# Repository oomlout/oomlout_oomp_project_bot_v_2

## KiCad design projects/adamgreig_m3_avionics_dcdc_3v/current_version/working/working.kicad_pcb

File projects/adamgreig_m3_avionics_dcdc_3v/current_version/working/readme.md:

# m3_avionics
 
## summary 
* id: adamgreig_m3_avionics_dcdc_3v
* user: adamgreig
* name: m3_avionics
* board: dcdc_3v
* repo: https://github.com/adamgreig/m3-avionics
* src_file_repo_kicad_pcb: m3psu/pcb/DCDC-3V/DCDC-3V.kicad_pcb
* src_file_repo_kicad_pcb_link: https://github.com/adamgreig/m3-avionics/tree/master/m3psu/pcb/DCDC-3V/DCDC-3V.kicad_pcb

* src_file_repo_sch: m3psu/pcb/DCDC-3V/DCDC-3V.sch
* src_file_repo_sch_link: https://github.com/adamgreig/m3-avionics/tree/master/m3psu/pcb/DCDC-3V/DCDC-3V.sch
* full details link: https://github.com/oomlout/oomlout_oomp_project_bot_v_2/tree/main/projects/adamgreig_m3_avionics_dcdc_3v/current_version/working  

## schematic  
  
[schematic (pdf)](working_schematic.pdf) 

## pcb  

[board (pdf)](working.pdf)  

## working_bom
| Id | Designator | Footprint | Quantity | Designation | Supplier and ref |  | None | 
| --- | --- | --- | --- | --- | --- | --- | --- | 
| 1 | J1 | TFML-110-02-L-D | 1 | WEST TOP |  |  | [''] | 
| 2 | J4 | TFML-110-02-L-D | 1 | EAST TOP |  |  | [''] | 
| 3 | J3 | TFML-105-02-L-D | 1 | NORTH TOP |  |  | [''] | 
| 4 | C5 | 0805 | 1 | 10u |  |  | [''] | 
| 5 | C6,C11,C1,C3,C4,C9,C12 | 0402 | 7 | 100n |  |  | [''] | 
| 6 | C7 | 0402 | 1 | 3n3 |  |  | [''] | 
| 7 | C8,C13 | 0805 | 2 | 22u |  |  | [''] | 
| 8 | C10,C2 | 0402 | 2 | 10n |  |  | [''] | 
| 9 | IC2 | QFN-16-EP-TI | 1 | TPS62132 |  |  | [''] | 
| 10 | IC1,IC3 | QFN-64-EP-LTC-UP | 2 | LTC2975 |  |  | [''] | 
| 11 | R2,R3,R4,R5,R6,R7,R8,R21,R22,R23,R24,R25,R27,R28 | 0402 | 14 | 10k |  |  | [''] | 
| 12 | R9,R10,R11,R12,R13,R14,R15,R16,R29,R30,R32,R33 | 0402 | 12 | 33k |  |  | [''] | 
| 13 | Q5,Q6,Q7,Q8,Q10,Q12 | SON2x2 | 6 | PFET_GDS |  |  | [''] | 
| 14 | R17,R18,R19,R20,R31,R34 | 0603 | 6 | 10m |  |  | [''] | 
| 15 | R1,R26 | 0402 | 2 | 5k49 |  |  | [''] | 
| 16 | Q1,Q2,Q3,Q4,Q9,Q11 | PowerPAK-SC-75-6L-Single | 6 | NFET_GDS |  |  | [''] | 
| 17 | L1 | XFL4020 | 1 | 2u2 |  |  | [''] | 
| 18 | R35,R36,R37,R38,R39,R40 | 0402 | 6 | 1M |  |  | [''] | 
| 19 | TP1,TP2,TP3,TP4 | TESTPAD | 4 | TESTPAD |  |  | [''] | 
| 20 | J2 | SFML-110-02-L-D-LC | 1 | WEST BOT |  |  | [''] | 
| 21 | J5 | SFML-110-02-L-D-LC | 1 | EAST BOT |  |  | [''] | 
| 22 | J6 | SFML-105-02-L-D-LC | 1 | NORTH BOT |  |  | [''] | 
| 23 | G*** | cusf_logo_full | 1 | LOGO |  |  | [''] | 

## bom_schematic
| Ref | Qnty | Value | Cmp name | Footprint | Description | Vendor | DNP | 
| --- | --- | --- | --- | --- | --- | --- | --- | 
| C1, C3, C4, C6, C9, C11, C12 | 7 | 100n | C | agg:0402 |  |  |  | 
| C2, C10 | 2 | 10n | C | agg:0402 |  |  |  | 
| C5 | 1 | 10u | C | agg:0805 |  |  |  | 
| C7 | 1 | 3n3 | C | agg:0402 |  |  |  | 
| C8, C13 | 2 | 22u | C | agg:0805 |  |  |  | 
| IC1, IC3 | 2 | LTC2975 | LTC2975 | agg:QFN-64-EP-LTC-UP |  |  |  | 
| IC2 | 1 | TPS62132 | TPS62132 | agg:QFN-16-EP-TI |  |  |  | 
| J1 | 1 | WEST TOP | CONN_02x10 | agg:TFML-110-02-L-D |  |  |  | 
| J2 | 1 | WEST BOT | CONN_02x10 | agg:SFML-110-02-L-D-LC |  |  |  | 
| J3 | 1 | NORTH TOP | CONN_02x05 | agg:TFML-105-02-L-D |  |  |  | 
| J4 | 1 | EAST TOP | CONN_02x10 | agg:TFML-110-02-L-D |  |  |  | 
| J5 | 1 | EAST BOT | CONN_02x10 | agg:SFML-110-02-L-D-LC |  |  |  | 
| J6 | 1 | NORTH BOT | CONN_02x05 | agg:SFML-105-02-L-D-LC |  |  |  | 
| L1 | 1 | 2u2 | L | agg:XFL4020 |  |  |  | 
| Q1, Q2, Q3, Q4, Q9, Q11 | 6 | NFET_GDS | NFET_GDS | agg:PowerPAK-SC-75-6L-Single |  |  |  | 
| Q5, Q6, Q7, Q8, Q10, Q12 | 6 | PFET_GDS | PFET_GDS | agg:SON2x2 |  |  |  | 
| R1, R26 | 2 | 5k49 | R | agg:0402 |  |  |  | 
| R2, R3, R4, R5, R6, R7, R8, R21, R22, R23, R24, R25, R27, R28 | 14 | 10k | R | agg:0402 |  |  |  | 
| R9, R10, R11, R12, R13, R14, R15, R16, R29, R30, R32, R33 | 12 | 33k | R | agg:0402 |  |  |  | 
| R17, R18, R19, R20, R31, R34 | 6 | 10m | R | agg:0603 |  |  |  | 
| R35, R36, R37, R38, R39, R40 | 6 | 1M | R | agg:0402 |  |  |  | 
| TP1, TP2, TP3, TP4 | 4 | TESTPAD | TESTPAD | agg:TESTPAD |  |  |  |

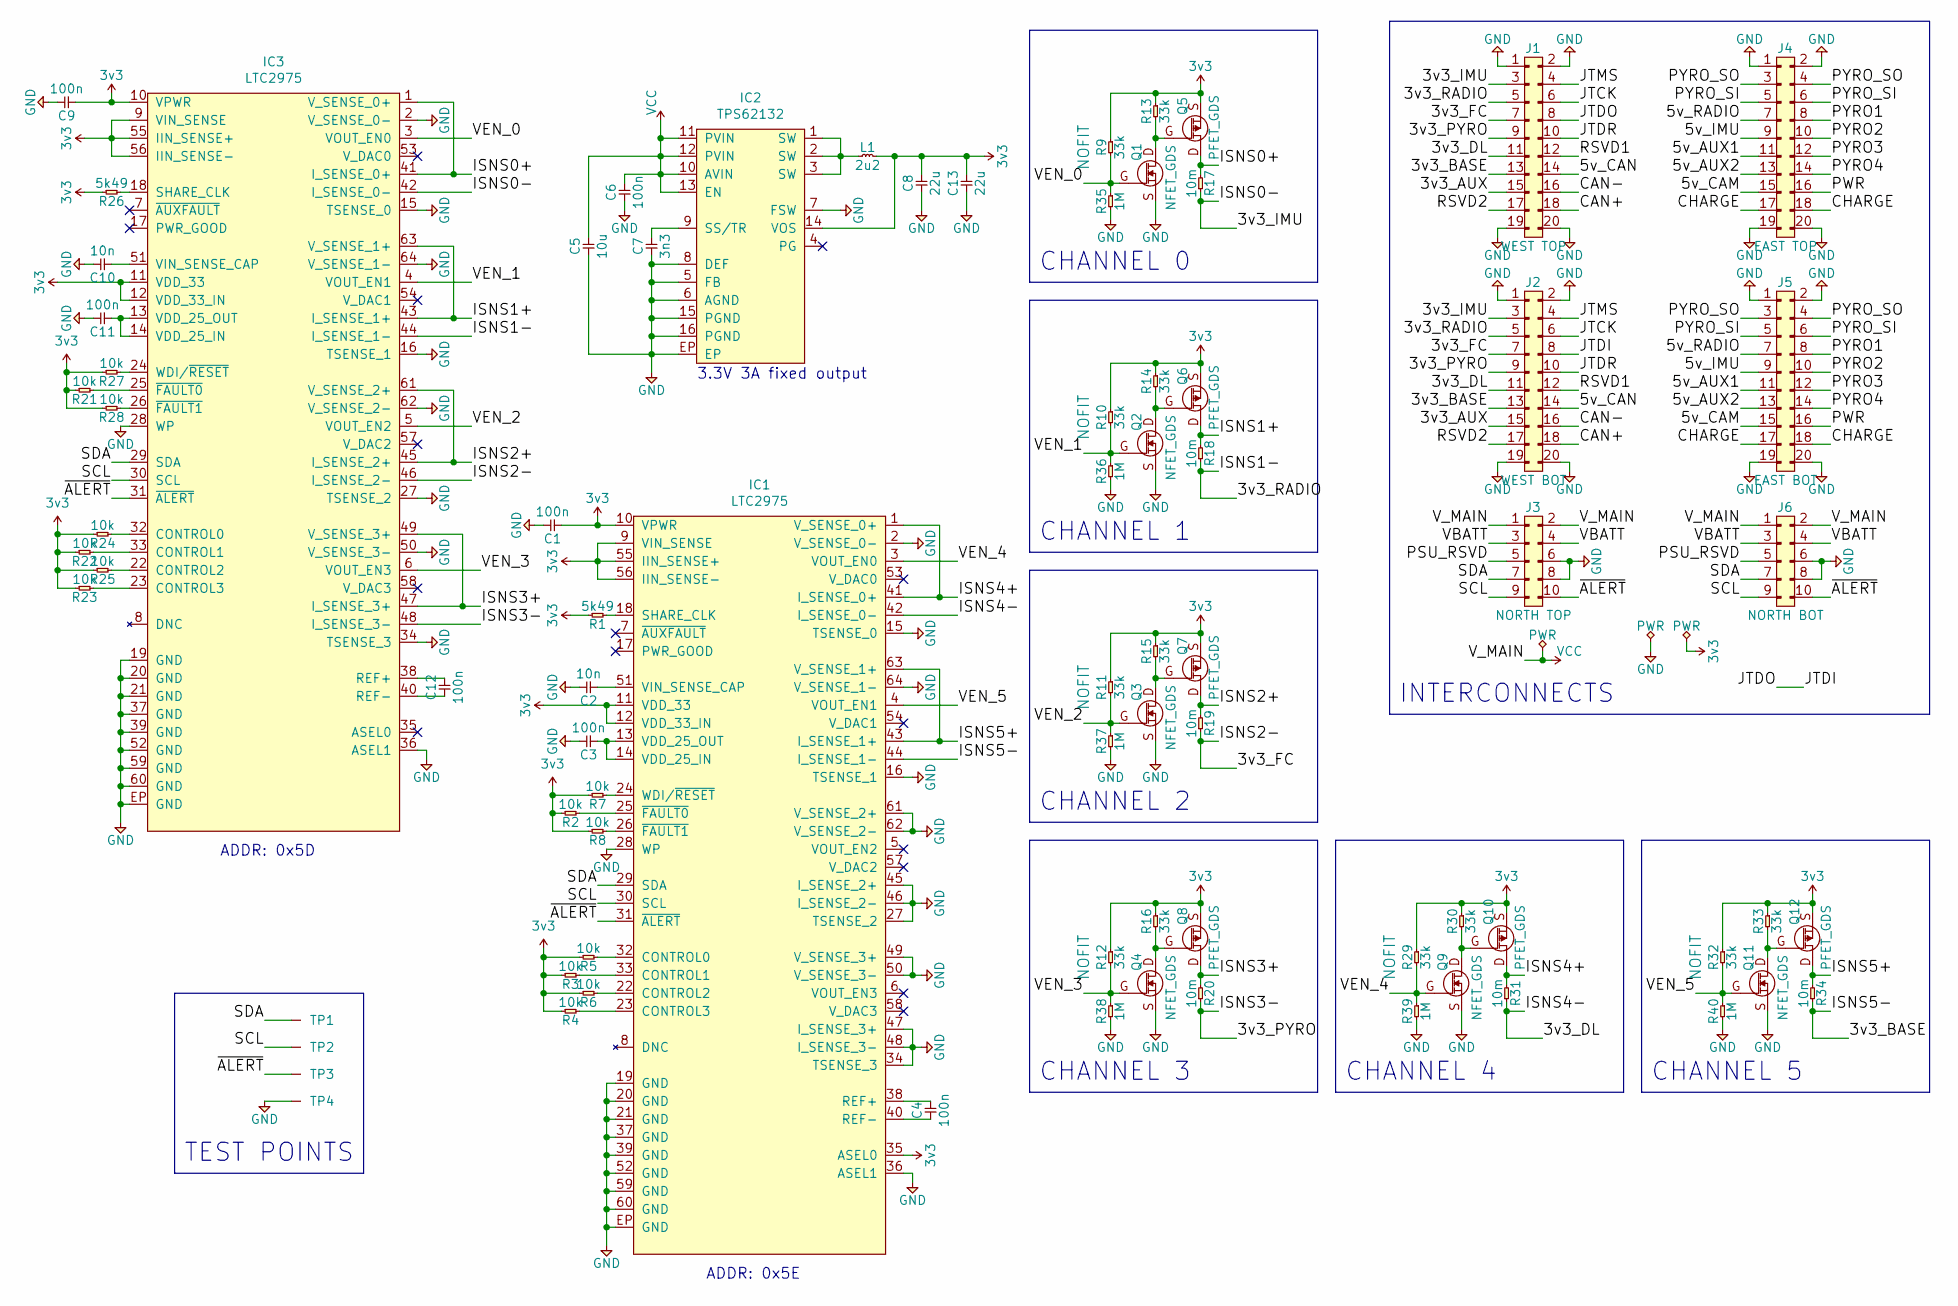
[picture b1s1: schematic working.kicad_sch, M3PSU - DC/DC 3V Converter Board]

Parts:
C1, C3, C4, C6, C9, C11, C12: 100n; 0402; Farnell 2496771
C2, C10: 10n; 0402; Farnell 1758924
C5: 10u; 0805; Farnell 2320856
C7: 3n3; 0402; Farnell 1758918
C8, C13: 22u; 0805; Farnell 1907510
IC1, IC3: LTC2975; QFN-64-EP-LTC-UP; Farnell 2461150
IC2: TPS62132; QFN-16-EP-TI; Farnell 2492468
J1: WEST TOP; TFML-110-02-L-D
J2: WEST BOT; SFML-110-02-L-D-LC
J3: NORTH TOP; TFML-105-02-L-D
J4: EAST TOP; TFML-110-02-L-D
J5: EAST BOT; SFML-110-02-L-D-LC
J6: NORTH BOT; SFML-105-02-L-D-LC
L1: 2u2; XFL4020; Farnell 2289216
Q1, Q2, Q3, Q4, Q9, Q11: NFET_GDS; PowerPAK-SC-75-6L-Single; Farnell 2364070
Q5, Q6, Q7, Q8, Q10, Q12: PFET_GDS; SON2x2; Farnell 2501102
R1, R26: 5k49; 0402; Farnell 2670533
R2, R3, R4, R5, R6, R7, R8, R21, R22, R23, R24, R25, R27, R28: 10k; 0402; Farnell 2447096
R9, R10, R11, R12, R29, R32: 33k; 0402
R13, R14, R15, R16, R30, R33: 33k; 0402; Farnell 2447160
R17, R18, R19, R20, R31, R34: 10m; 0603; Farnell RE05965
R35, R36, R37, R38, R39, R40: 1M; 0402; Farnell 2447127
TP1, TP2, TP3, TP4: TESTPAD

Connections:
3v3: C1.2, C8.1, C9.2, C13.1, IC1.9 (VIN_SENSE), IC1.10 (VPWR), IC1.11 (VDD_33), IC1.12 (VDD_33_IN), IC1.35 (ASEL0), IC1.55 (IIN_SENSE+), IC1.56 (IIN_SENSE-), IC2.14 (VOS), IC3.9 (VIN_SENSE), IC3.10 (VPWR), IC3.11 (VDD_33), IC3.12 (VDD_33_IN), IC3.55 (IIN_SENSE+), IC3.56 (IIN_SENSE-), L1.2, Q5.S, Q6.S, Q7.S, Q8.S, Q10.S, Q12.S, R1.1, R2.1, R3.1, R4.1, R5.1, R6.1, R7.1, R8.1, R9.1, R10.1, R11.1, R12.1, R13.1, R14.1, R15.1, R16.1, R21.1, R22.1, R23.1, R24.1, R25.1, R26.1, R27.1, R28.1, R29.1, R30.1, R32.1, R33.1
/3v3_AUX: J1.15, J2.15
/3v3_BASE: IC1.44 (I_SENSE_1-), J1.13, J2.13, R34.1
/3v3_DL: IC1.42 (I_SENSE_0-), J1.11, J2.11, R31.1
/3v3_FC: IC3.46 (I_SENSE_2-), J1.7, J2.7, R19.1
/3v3_IMU: IC3.42 (I_SENSE_0-), J1.3, J2.3, R17.1
/3v3_PYRO: IC3.48 (I_SENSE_3-), J1.9, J2.9, R20.1
/3v3_RADIO: IC3.44 (I_SENSE_1-), J1.5, J2.5, R18.1
/5v_AUX1: J4.11, J5.11
/5v_AUX2: J4.13, J5.13
/5v_CAM: J4.15, J5.15
/5v_CAN: J1.14, J2.14
/5v_IMU: J4.9, J5.9
/5v_RADIO: J4.7, J5.7
/CAN+: J1.18, J2.18
/CAN-: J1.16, J2.16
/CHARGE: J4.17, J4.18, J5.17, J5.18
/ISNS0+: IC3.1 (V_SENSE_0+), IC3.41 (I_SENSE_0+), Q5.D, R17.2
/ISNS1+: IC3.43 (I_SENSE_1+), IC3.63 (V_SENSE_1+), Q6.D, R18.2
/ISNS2+: IC3.45 (I_SENSE_2+), IC3.61 (V_SENSE_2+), Q7.D, R19.2
/ISNS3+: IC3.47 (I_SENSE_3+), IC3.49 (V_SENSE_3+), Q8.D, R20.2
/ISNS4+: IC1.1 (V_SENSE_0+), IC1.41 (I_SENSE_0+), Q10.D, R31.2
/ISNS5+: IC1.43 (I_SENSE_1+), IC1.63 (V_SENSE_1+), Q12.D, R34.2
/JTCK: J1.6, J2.6
/JTDI: J1.8, J2.8
/JTDR: J1.10, J2.10
/JTMS: J1.4, J2.4
/PSU_RSVD: J3.5, J6.5
/PWR: J4.16, J5.16
/PYRO1: J4.8, J5.8
/PYRO2: J4.10, J5.10
/PYRO3: J4.12, J5.12
/PYRO4: J4.14, J5.14
/PYRO_SI: J4.5, J4.6, J5.5, J5.6
/PYRO_SO: J4.3, J4.4, J5.3, J5.4
/RSVD1: J1.12, J2.12
/RSVD2: J1.17, J2.17
/SCL: IC1.30 (SCL), IC3.30 (SCL), J3.9, J6.9, TP2.1
/SDA: IC1.29 (SDA), IC3.29 (SDA), J3.7, J6.7, TP1.1
/VBATT: J3.3, J3.4, J6.3, J6.4
/VEN_0: IC3.3 (VOUT_EN0), Q1.G, R9.2, R35.1
/VEN_1: IC3.4 (VOUT_EN1), Q2.G, R10.2, R36.1
/VEN_2: IC3.5 (VOUT_EN2), Q3.G, R11.2, R37.1
/VEN_3: IC3.6 (VOUT_EN3), Q4.G, R12.2, R38.1
/VEN_4: IC1.3 (VOUT_EN0), Q9.G, R29.2, R39.1
/VEN_5: IC1.4 (VOUT_EN1), Q11.G, R32.2, R40.1
/~ALERT: IC1.31 (~ALERT), IC3.31 (~ALERT), J3.10, J6.10, TP3.1
GND: C1.1, C2.1, C3.1, C5.2, C6.2, C7.2, C8.2, C9.1, C10.1, C11.1, C13.2, IC1.2 (V_SENSE_0-), IC1.15 (TSENSE_0), IC1.16 (TSENSE_1), IC1.19 (GND), IC1.20 (GND), IC1.21 (GND), IC1.27 (TSENSE_2), IC1.28 (WP), IC1.34 (TSENSE_3), IC1.36 (ASEL1), IC1.37 (GND), IC1.39 (GND), IC1.45 (I_SENSE_2+), IC1.46 (I_SENSE_2-), IC1.47 (I_SENSE_3+), IC1.48 (I_SENSE_3-), IC1.49 (V_SENSE_3+), IC1.50 (V_SENSE_3-), IC1.52 (GND), IC1.59 (GND), IC1.60 (GND), IC1.61 (V_SENSE_2+), IC1.62 (V_SENSE_2-), IC1.64 (V_SENSE_1-), IC1.EP (GND), IC2.5 (FB), IC2.6 (AGND), IC2.7 (FSW), IC2.8 (DEF), IC2.15 (PGND), IC2.16 (PGND), IC2.EP, IC3.2 (V_SENSE_0-), IC3.15 (TSENSE_0), IC3.16 (TSENSE_1), IC3.19 (GND), IC3.20 (GND), IC3.21 (GND), IC3.27 (TSENSE_2), IC3.28 (WP), IC3.34 (TSENSE_3), IC3.36 (ASEL1), IC3.37 (GND), IC3.39 (GND), IC3.50 (V_SENSE_3-), IC3.52 (GND), IC3.59 (GND), IC3.60 (GND), IC3.62 (V_SENSE_2-), IC3.64 (V_SENSE_1-), IC3.EP (GND), J1.1, J1.2, J1.19, J1.20, J2.1, J2.2, J2.19, J2.20, J3.6, J3.8, J4.1, J4.2, J4.19, J4.20, J5.1, J5.2, J5.19, J5.20, J6.6, J6.8, Q1.S, Q2.S, Q3.S, Q4.S, Q9.S, Q11.S, R35.2, R36.2, R37.2, R38.2, R39.2, R40.2, TP4.1
unnamed: C2.2, IC1.51 (VIN_SENSE_CAP)
unnamed: C3.2, IC1.13 (VDD_25_OUT), IC1.14 (VDD_25_IN)
unnamed: C4.1, IC1.38 (REF+)
unnamed: C4.2, IC1.40 (REF-)
unnamed: C7.1, IC2.9 (SS/TR)
unnamed: C10.2, IC3.51 (VIN_SENSE_CAP)
unnamed: C11.2, IC3.13 (VDD_25_OUT), IC3.14 (VDD_25_IN)
unnamed: C12.1, IC3.38 (REF+)
unnamed: C12.2, IC3.40 (REF-)
unnamed: IC1.18 (SHARE_CLK), R1.2
unnamed: IC1.22 (CONTROL2), R6.2
unnamed: IC1.23 (CONTROL3), R4.2
unnamed: IC1.24 (WDI/~RESET), R7.2
unnamed: IC1.25 (~FAULT0), R2.2
unnamed: IC1.26 (~FAULT1), R8.2
unnamed: IC1.32 (CONTROL0), R5.2
unnamed: IC1.33 (CONTROL1), R3.2
unnamed: IC2.1 (SW), IC2.2 (SW), IC2.3 (SW), L1.1
unnamed: IC3.18 (SHARE_CLK), R26.2
unnamed: IC3.22 (CONTROL2), R25.2
unnamed: IC3.23 (CONTROL3), R23.2
unnamed: IC3.24 (WDI/~RESET), R27.2
unnamed: IC3.25 (~FAULT0), R21.2
unnamed: IC3.26 (~FAULT1), R28.2
unnamed: IC3.32 (CONTROL0), R24.2
unnamed: IC3.33 (CONTROL1), R22.2
unnamed: Q1.D, Q5.G, R13.2
unnamed: Q2.D, Q6.G, R14.2
unnamed: Q3.D, Q7.G, R15.2
unnamed: Q4.D, Q8.G, R16.2
unnamed: Q9.D, Q10.G, R30.2
unnamed: Q11.D, Q12.G, R33.2
VCC: C5.1, C6.1, IC2.10 (AVIN), IC2.11 (PVIN), IC2.12 (PVIN), IC2.13 (EN), J3.1, J3.2, J6.1, J6.2

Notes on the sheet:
CHANNEL 5
CHANNEL 4
CHANNEL 2
CHANNEL 1
ADDR: 0x5E
INTERCONNECTS
TEST POINTS
CHANNEL 0
CHANNEL 3
3.3V 3A fixed output
ADDR: 0x5D

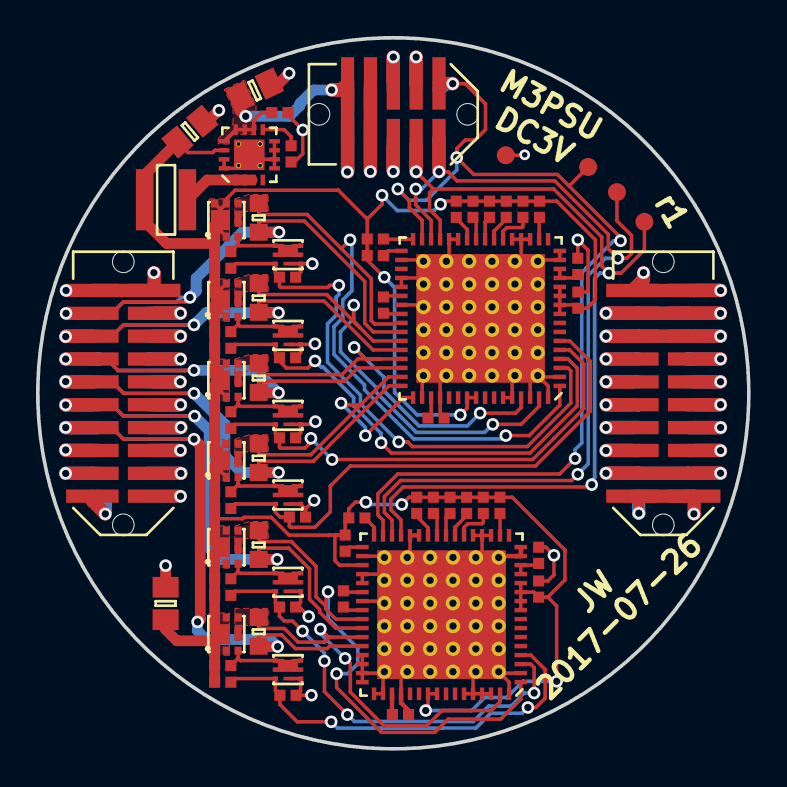
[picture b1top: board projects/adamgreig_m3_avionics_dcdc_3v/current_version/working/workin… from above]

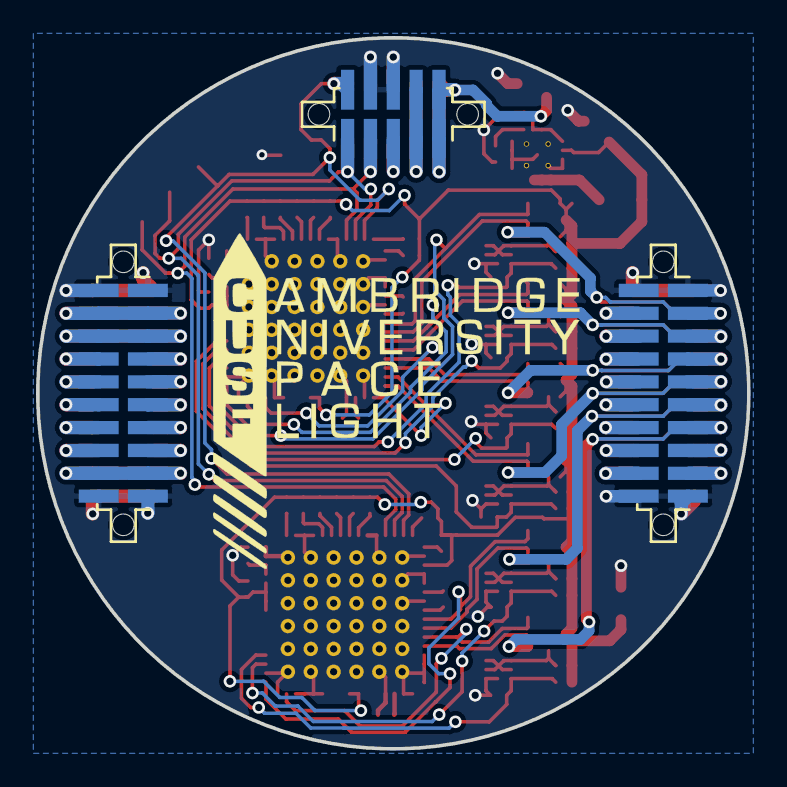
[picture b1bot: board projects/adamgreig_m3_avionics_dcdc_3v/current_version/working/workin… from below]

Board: 2 copper layers, 39.5 x 39.5 mm, 79 parts (3 on the bottom side), 81 nets.

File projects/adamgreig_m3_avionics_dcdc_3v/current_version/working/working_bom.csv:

"Id";"Designator";"Footprint";"Quantity";"Designation";"Supplier and ref";
1;"J1";"TFML-110-02-L-D";1;"WEST TOP";;;
2;"J4";"TFML-110-02-L-D";1;"EAST TOP";;;
3;"J3";"TFML-105-02-L-D";1;"NORTH TOP";;;
4;"C5";"0805";1;"10u";;;
5;"C6,C11,C1,C3,C4,C9,C12";"0402";7;"100n";;;
6;"C7";"0402";1;"3n3";;;
7;"C8,C13";"0805";2;"22u";;;
8;"C10,C2";"0402";2;"10n";;;
9;"IC2";"QFN-16-EP-TI";1;"TPS62132";;;
10;"IC1,IC3";"QFN-64-EP-LTC-UP";2;"LTC2975";;;
11;"R2,R3,R4,R5,R6,R7,R8,R21,R22,R23,R24,R25,R27,R28";"0402";14;"10k";;;
12;"R9,R10,R11,R12,R13,R14,R15,R16,R29,R30,R32,R33";"0402";12;"33k";;;
13;"Q5,Q6,Q7,Q8,Q10,Q12";"SON2x2";6;"PFET_GDS";;;
14;"R17,R18,R19,R20,R31,R34";"0603";6;"10m";;;
15;"R1,R26";"0402";2;"5k49";;;
16;"Q1,Q2,Q3,Q4,Q9,Q11";"PowerPAK-SC-75-6L-Single";6;"NFET_GDS";;;
17;"L1";"XFL4020";1;"2u2";;;
18;"R35,R36,R37,R38,R39,R40";"0402";6;"1M";;;
19;"TP1,TP2,TP3,TP4";"TESTPAD";4;"TESTPAD";;;
20;"J2";"SFML-110-02-L-D-LC";1;"WEST BOT";;;
21;"J5";"SFML-110-02-L-D-LC";1;"EAST BOT";;;
22;"J6";"SFML-105-02-L-D-LC";1;"NORTH BOT";;;
23;"G***";"cusf_logo_full";1;"LOGO";;;

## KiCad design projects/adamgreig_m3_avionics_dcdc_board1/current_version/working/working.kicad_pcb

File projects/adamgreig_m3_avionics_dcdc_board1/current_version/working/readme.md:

# m3_avionics
 
## summary 
* id: adamgreig_m3_avionics_dcdc_board1
* user: adamgreig
* name: m3_avionics
* board: dcdc_board1
* repo: https://github.com/adamgreig/m3-avionics
* src_file_repo_kicad_pcb: m3psu/pcb/DCDC-Board1/DCDC-Board1.kicad_pcb
* src_file_repo_kicad_pcb_link: https://github.com/adamgreig/m3-avionics/tree/master/m3psu/pcb/DCDC-Board1/DCDC-Board1.kicad_pcb

* src_file_repo_sch: m3psu/pcb/DCDC-5V/DCDC-5V.sch
* src_file_repo_sch_link: https://github.com/adamgreig/m3-avionics/tree/master/m3psu/pcb/DCDC-5V/DCDC-5V.sch
* full details link: https://github.com/oomlout/oomlout_oomp_project_bot_v_2/tree/main/projects/adamgreig_m3_avionics_dcdc_board1/current_version/working  

## schematic  
  
[schematic (pdf)](working_schematic.pdf) 

## pcb  

[board (pdf)](working.pdf)  

## working_bom
| Id | Designator | Footprint | Quantity | Designation | Supplier and ref |  | None | 
| --- | --- | --- | --- | --- | --- | --- | --- | 
| 1 | C1,C7,C15,C16,C22,C30 | 0805 | 6 | 22Âµ |  |  | [''] | 
| 2 | C2,C11,C13,C17,C26,C28,C31,C32 | 0402 | 8 | 100n |  |  | [''] | 
| 3 | C3,C12,C18,C27 | 0402 | 4 | 4n7 |  |  | [''] | 
| 4 | C5,C9,C20,C24 | 0402 | 4 | 220p |  |  | [''] | 
| 5 | C6,C8,C21,C23 | 0402 | 4 | 47p |  |  | [''] | 
| 6 | C10,C14,C25,C29 | 0402 | 4 | 1Âµ |  |  | [''] | 
| 7 | D1,D2,D3,D4 | 0603-LED | 4 | SCHOTTKY |  |  | [''] | 
| 8 | IC1,IC2 | QFN-40-EP-LTC-UJ | 2 | LTC3887 |  |  | [''] | 
| 9 | J1 | TFML-110-02-L-D | 1 | WEST TOP |  |  | [''] | 
| 10 | J4 | TFML-110-02-L-D | 1 | EAST TOP |  |  | [''] | 
| 11 | L1,L2,L3,L4 | TYS5040 | 4 | 10Âµ |  |  | [''] | 
| 12 | Q1,Q2,Q3,Q4 | PowerPair3x3 | 4 | SiZ340DT |  |  | [''] | 
| 13 | R1,R13,R14,R26 | 0603 | 4 | 50m |  |  | [''] | 
| 14 | R2,R15,R18,R20 | 0402 | 4 | 10k |  |  | [''] | 
| 15 | R3,R6,R9,R11,R16,R19,R22,R24 | 0402 | 8 | 100 |  |  | [''] | 
| 16 | R4,R12,R17,R25,R7,R5 | 0402 | 6 | 4k99 |  |  | [''] | 
| 17 | R8,R21 | 0402 | 2 | 24k9 |  |  | [''] | 
| 18 | R10 | 0402 | 1 | 5k76 |  |  | [''] | 
| 19 | R23 | 0402 | 1 | 7k32 |  |  | [''] | 
| 20 | J3 | TFML-105-02-L-D | 1 | NORTH TOP |  |  | [''] | 
| 21 | C19,C4 | 0402 | 2 | 4Âµ7 |  |  | [''] | 
| 22 | REF** | SIL-254P-01 | 1 | SIL-254P-01 |  |  | [''] | 
| 23 | J2 | SFML-110-02-L-D-LC | 1 | WEST BOT |  |  | [''] | 
| 24 | J5 | SFML-110-02-L-D-LC | 1 | EAST BOT |  |  | [''] | 
| 25 | J6 | SFML-105-02-L-D-LC | 1 | NORTH BOT |  |  | [''] | 
| 26 | G*** | cusf_logo_full | 1 | LOGO |  |  | [''] | 

## bom_schematic
| Ref | Qnty | Value | Cmp name | Footprint | Description | Vendor | DNP | 
| --- | --- | --- | --- | --- | --- | --- | --- | 
| J1 | 1 | WEST TOP | CONN_02x10 | agg:TFML-110-02-L-D |  |  |  | 
| J2 | 1 | WEST BOT | CONN_02x10 | agg:SFML-110-02-L-D-LC |  |  |  | 
| J3 | 1 | NORTH TOP | CONN_02x05 | agg:TFML-105-02-L-D |  |  |  | 
| J4 | 1 | EAST TOP | CONN_02x10 | agg:TFML-110-02-L-D |  |  |  | 
| J5 | 1 | EAST BOT | CONN_02x10 | agg:SFML-110-02-L-D-LC |  |  |  | 
| J6 | 1 | NORTH BOT | CONN_02x05 | agg:SFML-105-02-L-D-LC |  |  |  |

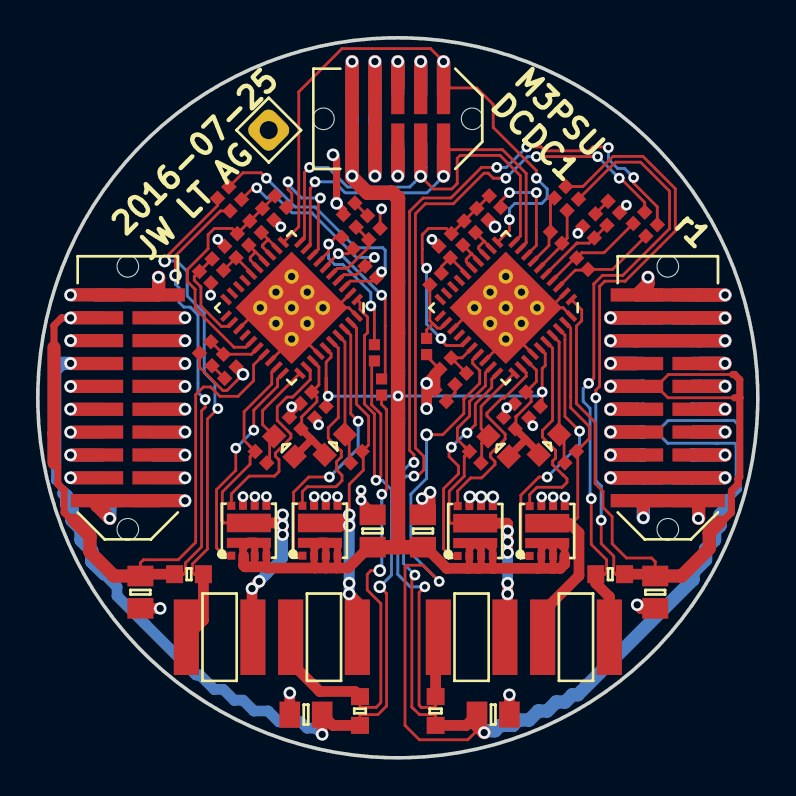
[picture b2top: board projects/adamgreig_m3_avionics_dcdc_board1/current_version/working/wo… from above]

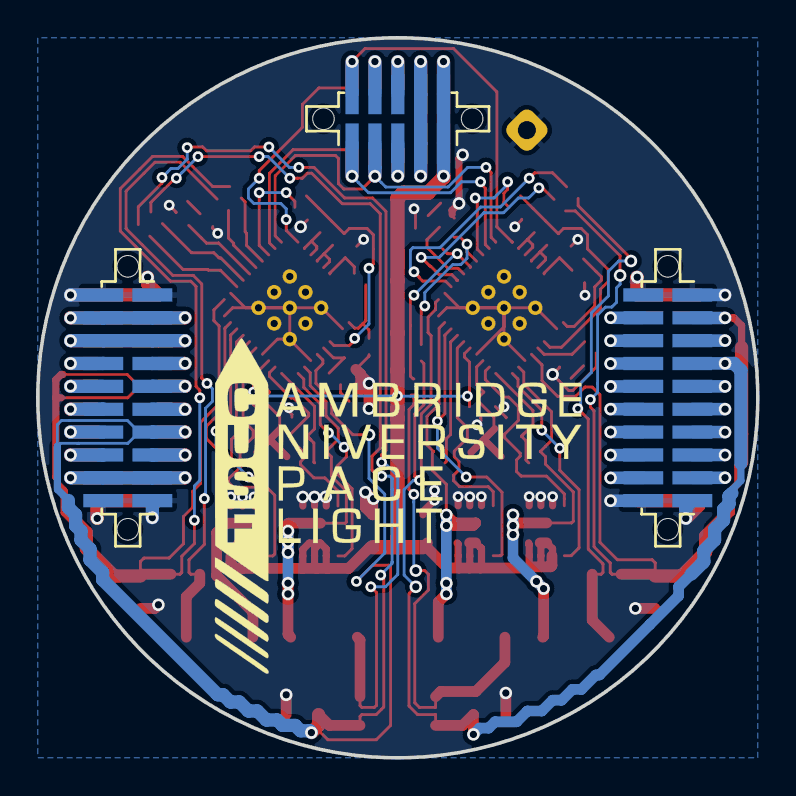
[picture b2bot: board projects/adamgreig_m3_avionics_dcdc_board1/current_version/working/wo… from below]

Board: 2 copper layers, 40.0 x 40.0 mm, 78 parts (3 on the bottom side), 88 nets.

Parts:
C1, C7, C15, C16, C22, C30: 22µ; 0805
C2, C11, C13, C17, C26, C28, C31, C32: 100n; 0402
C3, C12, C18, C27: 4n7; 0402
C4, C19: 4µ7; 0402
C5, C9, C20, C24: 220p; 0402
C6, C8, C21, C23: 47p; 0402
C10, C14, C25, C29: 1µ; 0402
D1, D2, D3, D4: SCHOTTKY; 0603-LED
IC1, IC2: LTC3887; QFN-40-EP-LTC-UJ
J1: WEST TOP; TFML-110-02-L-D
J2: WEST BOT; SFML-110-02-L-D-LC
J3: NORTH TOP; TFML-105-02-L-D
J4: EAST TOP; TFML-110-02-L-D
J5: EAST BOT; SFML-110-02-L-D-LC
J6: NORTH BOT; SFML-105-02-L-D-LC
L1, L2, L3, L4: 10µ; TYS5040
Q1, Q2, Q3, Q4: SiZ340DT; PowerPair3x3
R1, R13, R14, R26: 50m; 0603
R2, R15, R18, R20: 10k; 0402
R3, R6, R9, R11, R16, R19, R22, R24: 100; 0402
R4, R5, R7, R12, R17, R25: 4k99; 0402
R8, R21: 24k9; 0402
R10: 5k76; 0402
R23: 7k32; 0402

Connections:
3v3: J3.5, J6.5
/3v3_AUX1: J1.13, J2.13
/3v3_AUX2: J1.15, J2.15
/3v3_DL: J1.11, J2.11
/3v3_FC: C16.1, IC2.1, J1.7, J2.7, R14.1, R16.1
/3v3_IMU: C30.1, IC2.27, J1.3, J2.3, R24.2, R26.2
/3v3_PYRO: J1.9, J2.9
/3v3_RADIO: J1.5, J2.5
/5v_AUX1: J4.11, J5.11
/5v_AUX2: C15.1, IC1.27, J4.13, J5.13, R11.2, R13.2
/5v_CAM: J4.15, J5.15
/5v_CAN: J1.14, J2.14
/5v_IMU: C1.1, IC1.1, J4.9, J5.9, R1.1, R3.1
/5v_RADIO: J4.7, J5.7
/BATT1: J3.6, J6.6
/BATT2: J3.8, J6.8
/CAN+: J1.18, J2.18
/CAN-: J1.16, J2.16
/CHARGE: J4.17, J4.18, J5.17, J5.18
/JTCK: J1.6, J2.6
/JTDI: J1.8, J2.8
/JTDR: J1.10, J2.10
/JTMS: J1.4, J2.4
/PWR: J4.16, J5.16
/PYRO1: J4.8, J5.8
/PYRO2: J4.10, J5.10
/PYRO3: J4.12, J5.12
/PYRO4: J4.14, J5.14
/PYRO_SI: J4.5, J4.6, J5.5, J5.6
/PYRO_SO: J4.3, J4.4, J5.3, J5.4
/RSVD1: J1.12, J2.12
/RSVD2: J1.17, J2.17
/SCL: IC1.9, IC2.9, J3.9, J6.9
/SDA: IC1.10, IC2.10, J3.7, J6.7
/VBATT: J3.3, J3.4, J6.3, J6.4
/~ALERT: IC1.11, IC2.11, J3.10, J6.10
GND: C1.2, C4.2, C5.1, C7.2, C9.2, C10.2, C13.2, C14.2, C15.2, C16.2, C19.2, C20.1, C22.2, C24.2, C25.2, C28.2, C29.2, C30.2, C31.2, C32.2, IC1.2, IC1.23, IC1.28, IC1.34, IC1.40, IC1.EP, IC2.2, IC2.23, IC2.28, IC2.34, IC2.40, IC2.EP, J1.1, J1.2, J1.19, J1.20, J2.1, J2.2, J2.19, J2.20, J4.1, J4.2, J4.19, J4.20, J5.1, J5.2, J5.19, J5.20, Q1.S2, Q2.S2, Q3.S2, Q4.S2, R4.1, R10.2, R12.2, R17.1, R23.2, R25.2
unnamed: C2.1, IC1.39, L1.2, Q1.S1D2
unnamed: C2.2, D1.1, IC1.37
unnamed: C3.1, R4.2
unnamed: C3.2, C5.2, IC1.5
unnamed: C6.1, IC1.6, R6.2
unnamed: C6.2, IC1.7, R3.2
unnamed: C8.1, IC1.3, R9.1
unnamed: C8.2, IC1.4, R11.1
unnamed: C10.1, IC1.22, R8.2
unnamed: C11.1, D2.1, IC1.31
unnamed: C11.2, IC1.29, L2.1, Q2.S1D2
unnamed: C9.1, C12.1, IC1.26
unnamed: C12.2, R12.1
unnamed: C4.1, C13.1, D1.2, D2.2, IC1.33
unnamed: C14.1, IC1.25, R2.1, R5.1, R18.2
unnamed: C17.1, IC2.39, L3.2, Q3.S1D2
unnamed: C17.2, D3.1, IC2.37
unnamed: C18.1, R17.2
unnamed: C18.2, C20.2, IC2.5
unnamed: C19.1, C28.1, D3.2, D4.2, IC2.33
unnamed: C21.1, IC2.6, R19.2
unnamed: C21.2, IC2.7, R16.2
unnamed: C23.1, IC2.3, R22.1
unnamed: C23.2, IC2.4, R24.1
unnamed: C24.1, C27.1, IC2.26
unnamed: C25.1, IC2.22, R21.2
unnamed: C26.1, D4.1, IC2.31
unnamed: C26.2, IC2.29, L4.1, Q4.S1D2
unnamed: C27.2, R25.1
unnamed: C29.1, IC2.25, R7.1, R15.1, R20.2
unnamed: IC1.8, R5.2
unnamed: IC1.12, IC1.13, R18.1
unnamed: IC1.14, IC1.15, R2.2
unnamed: IC1.16, R8.1, R10.1
unnamed: IC1.30, Q2.G1
unnamed: IC1.32, Q2.G2
unnamed: IC1.36, Q1.G2
unnamed: IC1.38, Q1.G1
unnamed: IC2.8, R7.2
unnamed: IC2.12, IC2.13, R20.1
unnamed: IC2.14, IC2.15, R15.2
unnamed: IC2.16, R21.1, R23.1
unnamed: IC2.30, Q4.G1
unnamed: IC2.32, Q4.G2
unnamed: IC2.36, Q3.G2
unnamed: IC2.38, Q3.G1
unnamed: L1.1, R1.2, R6.1
unnamed: L2.2, R9.2, R13.1
unnamed: L3.1, R14.2, R19.1
unnamed: L4.2, R22.2, R26.1
VCC: C7.1, C22.1, C31.1, C32.1, IC1.35, IC2.35, J3.1, J3.2, J6.1, J6.2, Q1.D1, Q2.D1, Q3.D1, Q4.D1

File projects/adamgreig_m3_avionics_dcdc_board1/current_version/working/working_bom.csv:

"Id";"Designator";"Footprint";"Quantity";"Designation";"Supplier and ref";
1;"C1,C7,C15,C16,C22,C30";"0805";6;"22µ";;;
2;"C2,C11,C13,C17,C26,C28,C31,C32";"0402";8;"100n";;;
3;"C3,C12,C18,C27";"0402";4;"4n7";;;
4;"C5,C9,C20,C24";"0402";4;"220p";;;
5;"C6,C8,C21,C23";"0402";4;"47p";;;
6;"C10,C14,C25,C29";"0402";4;"1µ";;;
7;"D1,D2,D3,D4";"0603-LED";4;"SCHOTTKY";;;
8;"IC1,IC2";"QFN-40-EP-LTC-UJ";2;"LTC3887";;;
9;"J1";"TFML-110-02-L-D";1;"WEST TOP";;;
10;"J4";"TFML-110-02-L-D";1;"EAST TOP";;;
11;"L1,L2,L3,L4";"TYS5040";4;"10µ";;;
12;"Q1,Q2,Q3,Q4";"PowerPair3x3";4;"SiZ340DT";;;
13;"R1,R13,R14,R26";"0603";4;"50m";;;
14;"R2,R15,R18,R20";"0402";4;"10k";;;
15;"R3,R6,R9,R11,R16,R19,R22,R24";"0402";8;"100";;;
16;"R4,R12,R17,R25,R7,R5";"0402";6;"4k99";;;
17;"R8,R21";"0402";2;"24k9";;;
18;"R10";"0402";1;"5k76";;;
19;"R23";"0402";1;"7k32";;;
20;"J3";"TFML-105-02-L-D";1;"NORTH TOP";;;
21;"C19,C4";"0402";2;"4µ7";;;
22;"REF**";"SIL-254P-01";1;"SIL-254P-01";;;
23;"J2";"SFML-110-02-L-D-LC";1;"WEST BOT";;;
24;"J5";"SFML-110-02-L-D-LC";1;"EAST BOT";;;
25;"J6";"SFML-105-02-L-D-LC";1;"NORTH BOT";;;
26;"G***";"cusf_logo_full";1;"LOGO";;;
